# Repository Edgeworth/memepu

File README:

# Memepu

TODO fill out.

## Verymeme

### Example commands:

#### memecad

#### memelang
memelang ./src/memepile/{integral,memory,pointer,stdintf,vector,string,token,main}.meme

### Running tests
Run run.py to run the tests for both SCHEMATIC and non-SCHEMATIC verilog
configurations.

### Adding new symbols
Process for adding a new leaf module for verymeme:
1. Decide which Kicad symbol to use. If it's a new symbol, add data to
   pcb/kicadtools/ and generate using that.
2. Write a verilog module corresponding to that symbol
3. Write a mapping in memecad_map.json for the verilog module and kicad symbol.
4. Add it as a verilator module in verymeme/verilog/CMakeLists.txt
5. Add it to the SymbiYosys file in verymeme/verilog/formally_verify.sby

### Fuzzing
Build with:

export PFX=./

cmake -DUSE_AFL=yes -DCMAKE_BUILD_TYPE=Release $PFX/verymeme
AFL_SKIP_CPUFREQ=yes AFL_PRELOAD=/usr/local/lib/afl/libdislocator.so \
  afl-fuzz -m 1024M -i $PFX/verymeme/test_data/memelang/parsing -o memelang_fuzz \
  -x $PFX/verymeme/assets/afl/memelang.dict -- ./memelang @@

Or for persistent mode:
cmake -DUSE_AFL=clang -DCMAKE_BUILD_TYPE=Release $PFX/verymeme

AFL_SKIP_CPUFREQ=yes AFL_PRELOAD=/usr/local/lib/afl/libdislocator.so \
  afl-fuzz -m 1024M -i $PFX/verymeme/test_data/memelang/parsing -o memelang_fuzz \
  -x $PFX/verymeme/assets/afl/memelang.dict -t 100 -- ./memelang

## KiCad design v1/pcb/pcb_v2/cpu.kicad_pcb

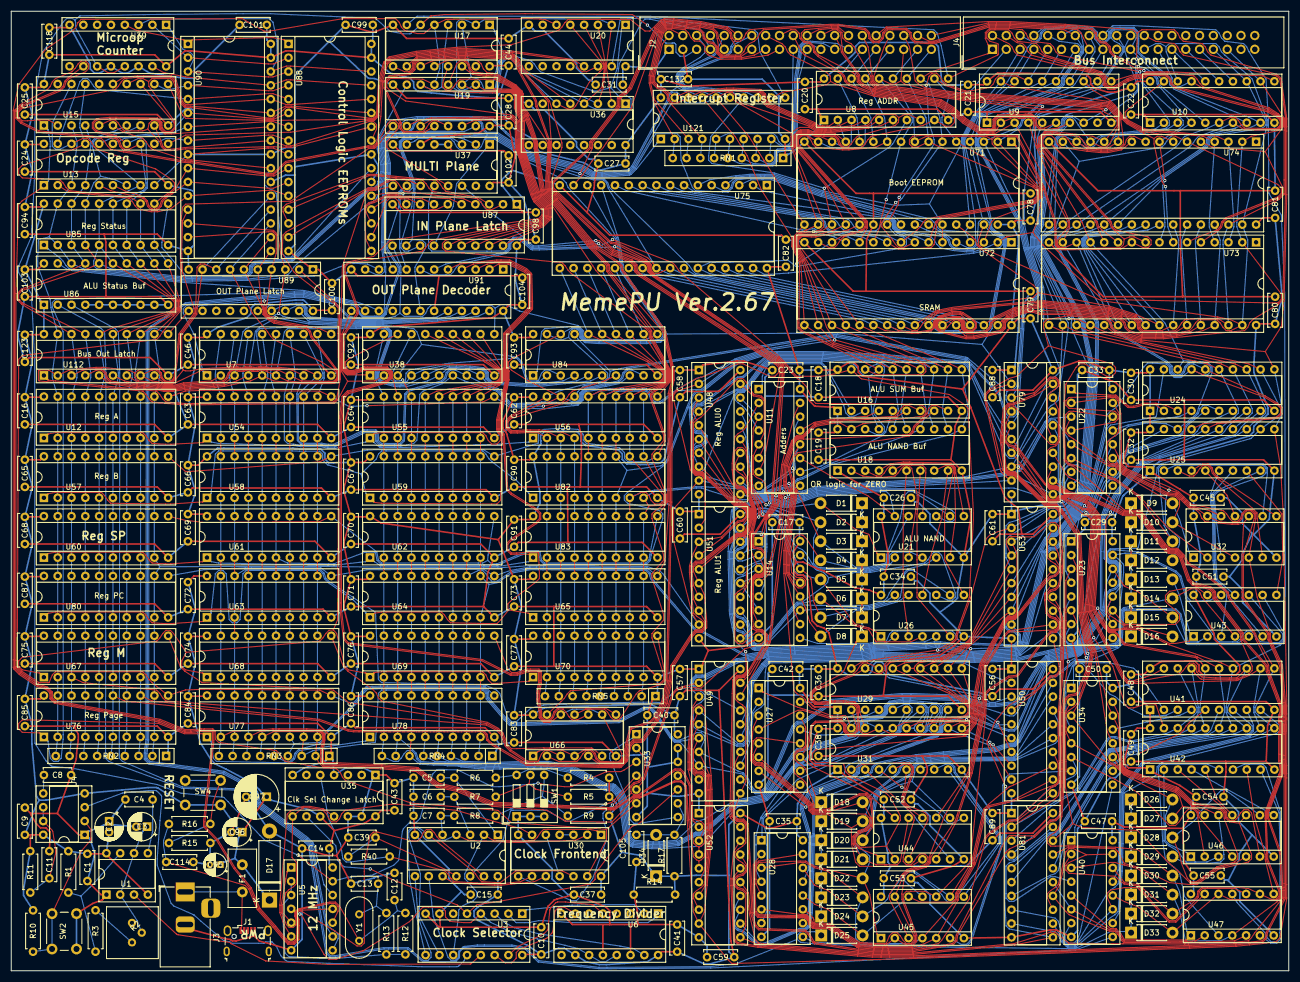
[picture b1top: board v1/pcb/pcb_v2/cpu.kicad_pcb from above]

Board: 2 copper layers, 235.0 x 176.5 mm, 268 parts (0 on the bottom side), 340 nets.

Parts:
C1, C5, C6, C7, C9, C10, C11, C14, C15, C16, C17, C18, C19, C20, C21, C22, C23, C24, C25, C26, C27, C28, C29, C30, C31, C32, C33, C34, C35, C36, C37, C38, C40, C41, C42, C43, C44, C45, C46, C47, C48, C49, C50, C51, C52, C53, C54, C55, C56, C57, C58, C59, C60, C61, C62, C63, C64, C65, C66, C67, C68, C69, C70, C71, C72, C73, C74, C75, C76, C77, C78, C79, C80, C81, C82, C83, C84, C85, C86, C87, C88, C89, C90, C91, C92, C93, C94, C98, C99, C100, C101, C102, C103, C104, C114, C118, C123, C132: 0.1uF; C_Disc_D6.0mm_W2.5mm_P5.00mm
C2, C3: 1uF; CP_Radial_D5.0mm_P2.00mm
C4, C8: 10nF; C_Disc_D5.0mm_W2.5mm_P5.00mm
C12, C13: 27pF; C_Disc_D4.7mm_W2.5mm_P5.00mm
C39: 1nF; C_Disc_D5.0mm_W2.5mm_P5.00mm
C95: 10uF; CP_Radial_D4.0mm_P2.00mm
C96: 100uF; CP_Radial_D5.0mm_P2.00mm
C97: 470uF; CP_Radial_D8.0mm_P3.80mm
C105: 10nF; C_Disc_D6.0mm_W2.5mm_P5.00mm
D1, D2, D3, D4, D5, D6, D7, D8, D9, D10, D11, D12, D13, D14, D15, D16, D18, D19, D20, D21, D22, D23, D24, D25, D26, D27, D28, D29, D30, D31, D32, D33, D34: D; D_DO-41_SOD81_P7.62mm_Horizontal
D17: 5.6V; D_5W_P12.70mm_Horizontal
F1: 0.65A; C_Disc_D10.5mm_W5.0mm_P5.00mm
J1: Conn_01x05; USB_Micro-B_Wuerth_629105150521
J2, J4: Conn_02x20_Odd_Even; IDC-Header_2x20_P2.54mm_Vertical
J3: Conn_01x03; BarrelJack_Horizontal
R1, R3, R13: 1K; R_Axial_DIN0207_L6.3mm_D2.5mm_P7.62mm_Horizontal
R2: 1M; Akizuki-Denshi Potentiometer
R4, R5, R9, R10, R14, R15: 100K; R_Axial_DIN0207_L6.3mm_D2.5mm_P7.62mm_Horizontal
R6, R7, R8, R11, R12, R16, R17, R40: 1M; R_Axial_DIN0207_L6.3mm_D2.5mm_P7.62mm_Horizontal
RN1: 10K; R_Array_SIP9
RN2, RN3, RN4, RN5: 100K; R_Array_SIP9
SW1: SW_DIP_x03 - Clock Source Select; SW_DIP_SPSTx03_Slide_9.78x9.8mm_W7.62mm_P2.54mm
SW2, SW4: SW_Push; SW_PUSH_6mm_H7.3mm
U1: LM555; DIP-8_W7.62mm_Socket
U2: 74HC14; DIP-14_W7.62mm_Socket
U3: 74151; DIP-16_W7.62mm_Socket
U4: LM555 - Button Clock; DIP-8_W7.62mm_Socket
U5: 74HC04; DIP-14_W7.62mm_Socket
U6, U39: 74HC590; DIP-16_W7.62mm_Socket
U7, U38, U84, U87, U89, U112: 74LS574; DIP-20_W7.62mm_Socket
U8, U9, U10, U12, U48, U49, U50, U51, U52, U53, U54, U55, U56, U57, U58, U59, U60, U61, U62, U63, U64, U65, U67, U68, U69, U70, U76, U77, U78, U79, U80, U81, U82, U83, U85, U121: 74HCT574; DIP-20_W7.62mm_Socket
U11, U14, U22, U23, U27, U28, U34, U40: 74LS283; DIP-16_W7.62mm_Socket
U13, U15: 74LS273; DIP-20_W7.62mm_Socket
U16, U18, U24, U25, U29, U31, U41, U42, U86: 74HC245; DIP-20_W7.62mm_Socket
U17, U19, U20, U36: 74HC238; DIP-16_W7.62mm_Socket
U21, U26, U32, U43, U44, U45, U46, U47: 74HC00; DIP-14_W7.62mm_Socket
U30: 74HC86; DIP-14_W7.62mm_Socket
U33: 74LS08; DIP-14_W7.62mm_Socket
U35: 74LS107; DIP-14_W7.62mm_Socket
U37: 74LS138; DIP-16_W7.62mm_Socket
U66: 74LS32; DIP-14_W7.62mm_Socket
U71, U88, U90: SST39SF040; DIP-32_W15.24mm_Socket
U72, U73, U74, U75: 628128; DIP-32_W15.24mm_Socket
U91: 74LS154; DIP-24_W7.62mm_Socket
Y1: 12MHz; Crystal_HC49-U_Vertical

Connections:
/ADDR0: J2.29, U8.19, U71.12
/ADDR1: J2.31, U8.18, U71.11
/ADDR2: J2.33, U8.17, U71.10, U72.12, U73.12, U74.12, U75.12
/ADDR3: J2.35, U8.16, U71.9, U72.11, U73.11, U74.11, U75.11
/ADDR4: J2.37, U8.15, U71.8, U72.10, U73.10, U74.10, U75.10
/ADDR5: J2.39, U8.14, U71.7, U72.9, U73.9, U74.9, U75.9
/ADDR6: J4.1, U8.13, U71.6, U72.8, U73.8, U74.8, U75.8
/ADDR7: J4.3, U8.12, U71.5, U72.7, U73.7, U74.7, U75.7
/ADDR8: J4.5, U9.19, U71.27, U72.6, U73.6, U74.6, U75.6
/ADDR9: J4.7, U9.18, U71.26, U72.5, U73.5, U74.5, U75.5
/ADDR10: J4.9, U9.17, U71.23, U72.27, U73.27, U74.27, U75.27
/ADDR11: J4.11, U9.16, U71.25, U72.26, U73.26, U74.26, U75.26
/ADDR12: J4.13, U9.15, U71.4, U72.23, U73.23, U74.23, U75.23
/ADDR13: J4.15, U9.14, U71.28, U72.25, U73.25, U74.25, U75.25
/ADDR14: J4.17, U9.13, U71.29, U72.4, U73.4, U74.4, U75.4
/ADDR15: J4.19, U9.12, U71.3, U72.28, U73.28, U74.28, U75.28
/ADDR16: J4.21, U10.19, U71.2, U72.3, U73.3, U74.3, U75.3
/ADDR17: J4.23, U10.18, U71.30, U72.31, U73.31, U74.31, U75.31
/ADDR18: J4.25, U10.17, U71.1, U72.2, U73.2, U74.2, U75.2
/ADDR19: J4.27, U10.16
/ADDR20: J4.29, U10.15
/ADDR21: J4.31, U10.14
/ADDR22: J4.33, U10.13, U72.22, U73.22, U74.22, U75.22
/ADDR23: J4.35, U10.12, U72.30, U73.30, U74.30, U75.30
/ADDR_IN_CLK: U8.11, U9.11, U10.11, U17.7
/ALU0_IN_CLK: U17.10, U48.11, U49.11, U50.11, U79.11
/ALU1_IN_CLK: U17.9, U51.11, U52.11, U53.11, U81.11
/ALU/A0: D1.2, U11.5, U21.1, U48.19
/ALU/A1: D2.2, U11.3, U21.4, U48.18
/ALU/A2: D3.2, U11.14, U21.9, U48.17
/ALU/A3: D4.2, U11.12, U21.12, U48.16
/ALU/A4: D5.2, U14.5, U26.1, U48.15
/ALU/A5: D6.2, U14.3, U26.4, U48.14
/ALU/A6: D7.2, U14.14, U26.9, U48.13
/ALU/A7: D8.2, U14.12, U26.12, U48.12
/ALU/A8: D9.2, U22.5, U32.1, U49.19
/ALU/A9: D10.2, U22.3, U32.4, U49.18
/ALU/A10: D11.2, U22.14, U32.9, U49.17
/ALU/A11: D12.2, U22.12, U32.12, U49.16
/ALU/A12: D13.2, U23.5, U43.1, U49.15
/ALU/A13: D14.2, U23.3, U43.4, U49.14
/ALU/A14: D15.2, U23.14, U43.9, U49.13
/ALU/A15: D16.2, U23.12, U43.12, U49.12
/ALU/A16: D18.2, U27.5, U44.1, U50.19
/ALU/A17: D19.2, U27.3, U44.4, U50.18
/ALU/A18: D20.2, U27.14, U44.9, U50.17
/ALU/A19: D21.2, U27.12, U44.12, U50.16
/ALU/A20: D22.2, U28.5, U45.1, U50.15
/ALU/A21: D23.2, U28.3, U45.4, U50.14
/ALU/A22: D24.2, U28.14, U45.9, U50.13
/ALU/A23: D25.2, U28.12, U45.12, U50.12
/ALU/A24: D26.2, U34.5, U46.1, U79.19
/ALU/A25: D27.2, U34.3, U46.4, U79.18
/ALU/A26: D28.2, U34.14, U46.9, U79.17
/ALU/A27: D29.2, U34.12, U46.12, U79.16
/ALU/A28: D30.2, U40.5, U47.1, U79.15
/ALU/A29: D31.2, U40.3, U47.4, U79.14
/ALU/A30: D32.2, U40.14, U47.9, U79.13
/ALU/A31: D33.2, U40.12, U47.12, U79.12
/ALU/B0: U11.6, U21.2, U51.19
/ALU/B1: U11.2, U21.5, U51.18
/ALU/B2: U11.15, U21.10, U51.17
/ALU/B3: U11.11, U21.13, U51.16
/ALU/B4: U14.6, U26.2, U51.15
/ALU/B5: U14.2, U26.5, U51.14
/ALU/B6: U14.15, U26.10, U51.13
/ALU/B7: U14.11, U26.13, U51.12
/ALU/B8: U22.6, U32.2, U52.19
/ALU/B9: U22.2, U32.5, U52.18
/ALU/B10: U22.15, U32.10, U52.17
/ALU/B11: U22.11, U32.13, U52.16
/ALU/B12: U23.6, U43.2, U52.15
/ALU/B13: U23.2, U43.5, U52.14
/ALU/B14: U23.15, U43.10, U52.13
/ALU/B15: U23.11, U43.13, U52.12
/ALU/B16: U27.6, U44.2, U53.19
/ALU/B17: U27.2, U44.5, U53.18
/ALU/B18: U27.15, U44.10, U53.17
/ALU/B19: U27.11, U44.13, U53.16
/ALU/B20: U28.6, U45.2, U53.15
/ALU/B21: U28.2, U45.5, U53.14
/ALU/B22: U28.15, U45.10, U53.13
/ALU/B23: U28.11, U45.13, U53.12
/ALU/B24: U34.6, U46.2, U81.19
/ALU/B25: U34.2, U46.5, U81.18
/ALU/B26: U34.15, U46.10, U81.17
/ALU/B27: U34.11, U46.13, U81.16
/ALU/B28: U40.6, U47.2, U81.15
/ALU/B29: U40.2, U47.5, U81.14
/ALU/B30: U40.15, U47.10, U81.13
/ALU/B31: U40.11, U47.13, U81.12
/ALU/CARRY0: U11.9, U14.7
/ALU/CARRY1: U14.9, U22.7
/ALU/CARRY2: U22.9, U23.7
/ALU/CARRY3: U23.9, U27.7
/ALU/CARRY4: U27.9, U28.7
/ALU/CARRY5: U28.9, U34.7
/ALU/CARRY6: U34.9, U40.7
/ALU/CARRY_OUT: U40.9, U86.2
/ALU/NAND0: U18.2, U21.3
/ALU/NAND1: U18.3, U21.6
/ALU/NAND2: U18.4, U21.8
/ALU/NAND3: U18.5, U21.11
/ALU/NAND4: U18.6, U26.3
/ALU/NAND5: U18.7, U26.6
/ALU/NAND6: U18.8, U26.8
/ALU/NAND7: U18.9, U26.11
/ALU/NAND8: U25.2, U32.3
/ALU/NAND9: U25.3, U32.6
/ALU/NAND10: U25.4, U32.8
/ALU/NAND11: U25.5, U32.11
/ALU/NAND12: U25.6, U43.3
/ALU/NAND13: U25.7, U43.6
/ALU/NAND14: U25.8, U43.8
/ALU/NAND15: U25.9, U43.11
/ALU/NAND16: U31.2, U44.3
/ALU/NAND17: U31.3, U44.6
/ALU/NAND18: U31.4, U44.8
/ALU/NAND19: U31.5, U44.11
/ALU/NAND20: U31.6, U45.3
/ALU/NAND21: U31.7, U45.6
/ALU/NAND22: U31.8, U45.8
/ALU/NAND23: U31.9, U45.11
/ALU/NAND24: U42.2, U46.3
/ALU/NAND25: U42.3, U46.6
/ALU/NAND26: U42.4, U46.8
/ALU/NAND27: U42.5, U46.11
/ALU/NAND28: U42.6, U47.3
/ALU/NAND29: U42.7, U47.6
/ALU/NAND30: U42.8, U47.8
/ALU/NAND31: U42.9, U47.11
/ALU/SUM0: U11.4, U16.2
/ALU/SUM1: U11.1, U16.3
/ALU/SUM2: U11.13, U16.4
/ALU/SUM3: U11.10, U16.5
/ALU/SUM4: U14.4, U16.6
/ALU/SUM5: U14.1, U16.7
/ALU/SUM6: U14.13, U16.8
/ALU/SUM7: U14.10, U16.9
/ALU/SUM8: U22.4, U24.2
/ALU/SUM9: U22.1, U24.3
/ALU/SUM10: U22.13, U24.4
/ALU/SUM11: U22.10, U24.5
/ALU/SUM12: U23.4, U24.6
/ALU/SUM13: U23.1, U24.7
/ALU/SUM14: U23.13, U24.8
/ALU/SUM15: U23.10, U24.9
/ALU/SUM16: U27.4, U29.2
/ALU/SUM17: U27.1, U29.3
/ALU/SUM18: U27.13, U29.4
/ALU/SUM19: U27.10, U29.5
/ALU/SUM20: U28.4, U29.6
/ALU/SUM21: U28.1, U29.7
/ALU/SUM22: U28.13, U29.8
/ALU/SUM23: U28.10, U29.9
/ALU/SUM24: U34.4, U41.2
/ALU/SUM25: U34.1, U41.3
/ALU/SUM26: U34.13, U41.4
/ALU/SUM27: U34.10, U41.5
/ALU/SUM28: U40.4, U41.6
/ALU/SUM29: U40.1, U41.7
/ALU/SUM30: U40.13, U41.8
/ALU/SUM31: U40.10, U41.9
/ALU/ZERO_OUT: U2.8, U86.3
/A_IN_CLK: U12.11, U17.14, U54.11, U55.11, U56.11
/BUS0: J2.2, RN2.9, U8.2, U12.2, U12.19, U13.3, U15.3, U16.18, U18.18, U48.2, U51.2, U57.2, U57.19, U60.2, U60.19, U67.2, U67.19, U71.13, U72.13, U76.2, U76.19, U80.2, U80.19, U85.2, U85.19, U86.18, U112.19, U121.19
/BUS1: J2.4, RN2.8, U8.3, U12.3, U12.18, U13.4, U15.4, U16.17, U18.17, U48.3, U51.3, U57.3, U57.18, U60.3, U60.18, U67.3, U67.18, U71.14, U72.14, U76.3, U76.18, U80.3, U80.18, U85.3, U85.18, U86.17, U112.18, U121.18
/BUS2: J2.6, RN2.7, U8.4, U12.4, U12.17, U13.7, U15.7, U16.16, U18.16, U48.4, U51.4, U57.4, U57.17, U60.4, U60.17, U67.4, U67.17, U71.15, U72.15, U76.4, U76.17, U80.4, U80.17, U85.4, U85.17, U86.16, U112.17, U121.17
/BUS3: J2.8, RN2.6, U8.5, U12.5, U12.16, U13.8, U15.8, U16.15, U18.15, U48.5, U51.5, U57.5, U57.16, U60.5, U60.16, U67.5, U67.16, U71.17, U72.17, U76.5, U76.16, U80.5, U80.16, U85.5, U85.16, U86.15, U112.16, U121.16
/BUS4: J2.10, RN2.5, U8.6, U12.6, U12.15, U13.13, U15.13, U16.14, U18.14, U48.6, U51.6, U57.6, U57.15, U60.6, U60.15, U67.6, U67.15, U71.18, U72.18, U76.6, U76.15, U80.6, U80.15, U85.6, U85.15, U86.14, U112.15, U121.15
/BUS5: J2.12, RN2.4, U8.7, U12.7, U12.14, U13.14, U15.14, U16.13, U18.13, U48.7, U51.7, U57.7, U57.14, U60.7, U60.14, U67.7, U67.14, U71.19, U72.19, U76.7, U76.14, U80.7, U80.14, U85.7, U85.14, U86.13, U112.14, U121.14
/BUS6: J2.14, RN2.3, U8.8, U12.8, U12.13, U13.17, U15.17, U16.12, U18.12, U48.8, U51.8, U57.8, U57.13, U60.8, U60.13, U67.8, U67.13, U71.20, U72.20, U76.8, U76.13, U80.8, U80.13, U85.8, U85.13, U86.12, U112.13, U121.13
/BUS7: J2.16, RN2.2, U8.9, U12.9, U12.12, U13.18, U15.18, U16.11, U18.11, U48.9, U51.9, U57.9, U57.12, U60.9, U60.12, U67.9, U67.12, U71.21, U72.21, U76.9, U76.12, U80.9, U80.12, U85.9, U85.12, U86.11, U112.12, U121.12
/BUS8: J2.18, RN3.9, U7.19, U9.2, U24.18, U25.18, U49.2, U52.2, U54.2, U54.19, U58.2, U58.19, U61.2, U61.19, U63.2, U63.19, U68.2, U68.19, U73.13, U77.2, U77.19
/BUS9: J2.20, RN3.8, U7.18, U9.3, U24.17, U25.17, U49.3, U52.3, U54.3, U54.18, U58.3, U58.18, U61.3, U61.18, U63.3, U63.18, U68.3, U68.18, U73.14, U77.3, U77.18
/BUS10: J2.22, RN3.7, U7.17, U9.4, U24.16, U25.16, U49.4, U52.4, U54.4, U54.17, U58.4, U58.17, U61.4, U61.17, U63.4, U63.17, U68.4, U68.17, U73.15, U77.4, U77.17
/BUS11: J2.24, RN3.6, U7.16, U9.5, U24.15, U25.15, U49.5, U52.5, U54.5, U54.16, U58.5, U58.16, U61.5, U61.16, U63.5, U63.16, U68.5, U68.16, U73.17, U77.5, U77.16
/BUS12: J2.26, RN3.5, U7.15, U9.6, U24.14, U25.14, U49.6, U52.6, U54.6, U54.15, U58.6, U58.15, U61.6, U61.15, U63.6, U63.15, U68.6, U68.15, U73.18, U77.6, U77.15
/BUS13: J2.28, RN3.4, U7.14, U9.7, U24.13, U25.13, U49.7, U52.7, U54.7, U54.14, U58.7, U58.14, U61.7, U61.14, U63.7, U63.14, U68.7, U68.14, U73.19, U77.7, U77.14
/BUS14: J2.30, RN3.3, U7.13, U9.8, U24.12, U25.12, U49.8, U52.8, U54.8, U54.13, U58.8, U58.13, U61.8, U61.13, U63.8, U63.13, U68.8, U68.13, U73.20, U77.8, U77.13
/BUS15: J2.32, RN3.2, U7.12, U9.9, U24.11, U25.11, U49.9, U52.9, U54.9, U54.12, U58.9, U58.12, U61.9, U61.12, U63.9, U63.12, U68.9, U68.12, U73.21, U77.9, U77.12
/BUS16: J2.34, RN4.9, U10.2, U29.18, U31.18, U38.19, U50.2, U53.2, U55.2, U55.19, U59.2, U59.19, U62.2, U62.19, U64.2, U64.19, U69.2, U69.19, U74.13, U78.2, U78.19
/BUS17: J2.36, RN4.8, U10.3, U29.17, U31.17, U38.18, U50.3, U53.3, U55.3, U55.18, U59.3, U59.18, U62.3, U62.18, U64.3, U64.18, U69.3, U69.18, U74.14, U78.3, U78.18
/BUS18: J2.38, RN4.7, U10.4, U29.16, U31.16, U38.17, U50.4, U53.4, U55.4, U55.17, U59.4, U59.17, U62.4, U62.17, U64.4, U64.17, U69.4, U69.17, U74.15, U78.4, U78.17
/BUS19: J2.40, RN4.6, U10.5, U29.15, U31.15, U38.16, U50.5, U53.5, U55.5, U55.16, U59.5, U59.16, U62.5, U62.16, U64.5, U64.16, U69.5, U69.16, U74.17, U78.5, U78.16
/BUS20: J4.2, RN4.5, U10.6, U29.14, U31.14, U38.15, U50.6, U53.6, U55.6, U55.15, U59.6, U59.15, U62.6, U62.15, U64.6, U64.15, U69.6, U69.15, U74.18, U78.6, U78.15
/BUS21: J4.4, RN4.4, U10.7, U29.13, U31.13, U38.14, U50.7, U53.7, U55.7, U55.14, U59.7, U59.14, U62.7, U62.14, U64.7, U64.14, U69.7, U69.14, U74.19, U78.7, U78.14
/BUS22: J4.6, RN4.3, U10.8, U29.12, U31.12, U38.13, U50.8, U53.8, U55.8, U55.13, U59.8, U59.13, U62.8, U62.13, U64.8, U64.13, U69.8, U69.13, U74.20, U78.8, U78.13
/BUS23: J4.8, RN4.2, U10.9, U29.11, U31.11, U38.12, U50.9, U53.9, U55.9, U55.12, U59.9, U59.12, U62.9, U62.12, U64.9, U64.12, U69.9, U69.12, U74.21, U78.9, U78.12
/BUS24: J4.10, RN5.9, U41.18, U42.18, U56.2, U56.19, U65.2, U65.19, U70.2, U70.19, U75.13, U79.2, U81.2, U82.2, U82.19, U83.2, U83.19, U84.19
/BUS25: J4.12, RN5.8, U41.17, U42.17, U56.3, U56.18, U65.3, U65.18, U70.3, U70.18, U75.14, U79.3, U81.3, U82.3, U82.18, U83.3, U83.18, U84.18
/BUS26: J4.14, RN5.7, U41.16, U42.16, U56.4, U56.17, U65.4, U65.17, U70.4, U70.17, U75.15, U79.4, U81.4, U82.4, U82.17, U83.4, U83.17, U84.17
/BUS27: J4.16, RN5.6, U41.15, U42.15, U56.5, U56.16, U65.5, U65.16, U70.5, U70.16, U75.17, U79.5, U81.5, U82.5, U82.16, U83.5, U83.16, U84.16
/BUS28: J4.18, RN5.5, U41.14, U42.14, U56.6, U56.15, U65.6, U65.15, U70.6, U70.15, U75.18, U79.6, U81.6, U82.6, U82.15, U83.6, U83.15, U84.15
/BUS29: J4.20, RN5.4, U41.13, U42.13, U56.7, U56.14, U65.7, U65.14, U70.7, U70.14, U75.19, U79.7, U81.7, U82.7, U82.14, U83.7, U83.14, U84.14
/BUS30: J4.22, RN5.3, U41.12, U42.12, U56.8, U56.13, U65.8, U65.13, U70.8, U70.13, U75.20, U79.8, U81.8, U82.8, U82.13, U83.8, U83.13, U84.13
/BUS31: J4.24, RN5.2, U41.11, U42.11, U56.9, U56.12, U65.9, U65.12, U70.9, U70.12, U75.21, U79.9, U81.9, U82.9, U82.12, U83.9, U83.12, U84.12
/B_IN_CLK: U17.13, U57.11, U58.11, U59.11, U82.11
/CARRY_IN: U11.7, U37.12
/CLK: J2.5, U5.13, U17.6, U33.3, U39.11, U39.13
/Clock/1.5MHZ_CLK: U3.1, U6.2
/Clock/3MHZ_CLK: U3.2, U6.1
/Clock/6MHZ_CLK: U3.3, U6.15
/Clock/12MHZ_CLK: U3.4, U5.4, U6.11, U6.13
/Clock/47_KHZ_CLK: U3.14, U6.7
/Clock/187KHZ_CLK: U3.15, U6.5
/Clock/AC_TR: C3.1, R2.2, U1.2, U1.6
/Clock/ADJ_CLK: U1.3, U3.13
/Clock/BTN_CLK: U3.12, U4.3
/Clock/PRE_CLK: U3.5, U33.10, U35.9
/Clock/SEL0: U2.2, U3.11, U30.1
/Clock/SEL1: U2.4, U3.10, U30.2
/Clock/SEL2: U2.6, U3.9, U30.12
/Control Logic/CTRL0: U87.2, U88.13
/Control Logic/CTRL1: U87.3, U88.14
/Control Logic/CTRL2: U87.4, U88.15
/Control Logic/CTRL3: U87.5, U88.17
/Control Logic/CTRL4: U87.6, U88.18
/Control Logic/CTRL5: U87.7, U88.19
/Control Logic/CTRL6: U87.8, U88.20
/Control Logic/CTRL7: U87.9, U88.21
/Control Logic/CTRL8: U7.2, U38.2, U84.2, U89.2, U90.13, U112.2
/Control Logic/CTRL9: U7.3, U38.3, U84.3, U89.3, U90.14, U112.3
/Control Logic/CTRL10: U7.4, U38.4, U84.4, U89.4, U90.15, U112.4
/Control Logic/CTRL11: U7.5, U38.5, U84.5, U89.5, U90.17, U112.5
/Control Logic/CTRL12: U7.6, U38.6, U84.6, U89.6, U90.18, U112.6
/Control Logic/CTRL13: U7.7, U38.7, U84.7, U89.7, U90.19, U112.7
/Control Logic/CTRL14: U7.8, U38.8, U84.8, U89.8, U90.20, U112.8
/Control Logic/CTRL15: U7.9, U38.9, U84.9, U89.9, U90.21, U112.9
/Control Logic/CTRL_IN0: U17.1, U19.1, U20.1, U36.1, U87.19
/Control Logic/CTRL_IN1: U17.2, U19.2, U20.2, U36.2, U87.18
/Control Logic/CTRL_IN2: U17.3, U19.3, U20.3, U36.3, U87.17
/Control Logic/CTRL_IN3: U17.4, U19.6, U20.5, U36.6, U87.16
/Control Logic/CTRL_IN4: U5.11, U17.5, U19.5, U20.6, U87.15
/Control Logic/CTRL_MULTI0: U37.1, U87.14
/Control Logic/CTRL_MULTI1: U37.2, U87.13
/Control Logic/CTRL_MULTI2: U37.3, U87.12, U91.18
/Control Logic/CTRL_OUT0: U89.19, U91.23
/Control Logic/CTRL_OUT1: U89.18, U91.22
/Control Logic/CTRL_OUT2: U89.17, U91.21
/Control Logic/CTRL_OUT3: U89.16, U91.20
/Control Logic/IN decoder/~S4: U5.10, U36.5
/Control Logic/MICROOP0: U39.15, U88.29, U90.29
/Control Logic/MICROOP1: U39.1, U88.3, U90.3
/Control Logic/MICROOP2: U39.2, U88.2, U90.2
/Control Logic/MICROOP3: U39.3, U88.30, U90.30
/Control Logic/MICROOP4: U39.4, U88.1, U90.1
/Control Logic/MMU_IN_CLK: U5.9, U19.15
/Control Logic/OP0: U13.2, U88.12, U90.12
/Control Logic/OP1: U13.5, U88.11, U90.11
/Control Logic/OP2: U13.6, U88.10, U90.10
/Control Logic/OP3: U13.9, U88.9, U90.9
/Control Logic/OP4: U13.12, U88.8, U90.8
/Control Logic/OP5: U13.15, U88.7, U90.7
/Control Logic/OP6: U13.16, U88.6, U90.6
/Control Logic/OP7: U13.19, U88.5, U90.5
/Control Logic/OP8: U15.2, U88.27, U90.27
/Control Logic/OP9: U15.5, U88.26, U90.26
/Control Logic/OP10: U15.6, U88.23, U90.23
/Control Logic/OP11: U15.9, U88.25, U90.25
/Control Logic/OP12: U15.12, U88.4, U90.4
/Control Logic/OP13: U15.15, U88.28, U90.28
/Control Logic/OPCODE0_IN_CLK: U13.11, U20.14
/Control Logic/OPCODE1_IN_CLK: U15.11, U20.13
/Control Logic/~BUS0_OUT_NCLK: U37.11, U112.1
/Control Logic/~BUS1_OUT_NCLK: U7.1, U37.10
/Control Logic/~BUS2_OUT_NCLK: U37.9, U38.1
/Control Logic/~BUS3_OUT_NCLK: U37.7, U84.1
/Control Logic/~RESET_UOP_COUNT_NCLK: U37.13, U39.10
/INT0: J2.13, RN1.9, U121.2
/INT1: J2.15, RN1.8, U121.3
/INT2: J2.17, RN1.7, U121.4
/INT3: J2.19, RN1.6, U121.5
/INT4: J2.21, RN1.5, U121.6
/INT5: J2.23, RN1.4, U121.7
/INT6: J2.25, RN1.3, U121.8
/INT7: J2.27, RN1.2, U121.9
/INT_IN_CLK: U20.15, U121.11
/M0_IN_CLK: U19.13, U66.2
/M1_IN_CLK: U19.12, U66.5
/M2_IN_CLK: U19.11, U66.10
/M3_IN_CLK: U19.10, U66.13
/M_IN_CLK: U19.14, U66.1, U66.4, U66.9, U66.12
/PAGE_IN_CLK: U19.9, U76.11, U77.11, U78.11
/PC_IN_CLK: U17.11, U63.11, U64.11, U65.11, U80.11
/Registers/Register M/REG_IN0_OR: U66.3, U67.11
/Registers/Register M/REG_IN1_OR: U66.6, U68.11
/Registers/Register M/REG_IN2_OR: U66.8, U69.11
/Registers/Register M/REG_IN3_OR: U66.11, U70.11
/SP_IN_CLK: U17.12, U60.11, U61.11, U62.11, U83.11
/STATUS_IN_CLK: U19.7, U85.11
/~ALU_STATUS_OUT_NCLK: U86.19, U91.15
/~A_OUT_NCLK: U12.1, U54.1, U55.1, U56.1, U91.2
/~B_OUT_NCLK: U57.1, U58.1, U59.1, U82.1, U91.3
/~CLK: J2.7, U5.12, U7.11, U19.4, U20.4, U36.4, U38.11, U84.11, U87.11, U89.11, U112.11
/~EEPROM_OUT_NCLK: U71.24, U91.11
/~INT_OUT_NCLK: U91.9, U121.1
/~MMU_IN_CLK: J2.9, U5.8, U72.29, U73.29, U74.29, U75.29
/~MMU_OUT_NCLK: J2.11, U72.24, U73.24, U74.24, U75.24, U91.8
/~M_OUT_NCLK: U67.1, U68.1, U69.1, U70.1, U91.13
/~NAND_OUT_NCLK: U18.19, U25.19, U31.19, U42.19, U91.7
/~PAGE_OUT_NCLK: U76.1, U77.1, U78.1, U91.14
/~PC_OUT_NCLK: U63.1, U64.1, U65.1, U80.1, U91.5
/~RESET: U13.1, U15.1, U30.13, U33.6
/~RESET_NCLK: U33.5, U37.14
/~SP_OUT_NCLK: U60.1, U61.1, U62.1, U83.1, U91.4
/~STATUS_OUT_NCLK: U85.1, U91.10
/~SUM_OUT_NCLK: U16.19, U24.19, U29.19, U41.19, U91.6
GND: C1.2, C2.1, C3.2, C4.2, C5.1, C6.1, C7.1, C8.2, C9.2, C10.2, C11.1, C12.2, C13.2, C14.2, C15.1, C16.2, C17.2, C18.2, C19.2, C20.2, C21.2, C22.2, C23.2, C24.1, C25.1, C26.2, C27.1, C28.1, C29.2, C30.2, C31.1, C32.2, C33.2, C34.2, C35.2, C36.2, C37.1, C38.2, C39.2, C40.1, C41.1, C42.2, C43.1, C44.1, C45.2, C46.1, C47.2, C48.2, C49.2, C50.2, C51.2, C52.2, C53.2, C54.2, C55.2, C56.2, C57.2, C58.2, C59.2, C60.2, C61.2, C62.2, C63.2, C64.2, C65.2, C66.2, C67.2, C68.2, C69.2, C70.2, C71.2, C72.2, C73.2, C74.2, C75.2, C76.2, C77.2, C78.1, C79.1, C80.1, C81.1, C82.1, C83.2, C84.2, C85.2, C86.2, C87.2, C88.2, C89.2, C90.2, C91.2, C92.1, C93.1, C94.2, C95.2, C96.2, C97.2, C98.1, C99.1, C100.1, C101.1, C102.1, C103.2, C104.1, C105.1, C114.1, C118.1, C123.1, C132.2, D17.2, J1.5, J2.3, J3.2, R14.1, R15.2, RN1.1, RN2.1, RN3.1, RN4.1, RN5.1, SW1.1, SW1.2, SW1.3, SW2.1, U1.1, U2.7, U3.7, U3.8, U4.1, U5.7, U6.8, U6.12, U6.14, U7.10, U8.1, U8.10, U9.1, U9.10, U10.1, U10.10, U11.8, U12.10, U13.10, U14.8, U15.10, U16.10, U17.8, U18.10, U19.8, U20.8, U21.7, U22.8, U23.8, U24.10, U25.10, U26.7, U27.8, U28.8, U29.10, U30.7, U31.10, U32.7, U33.7, U33.12, U33.13, U34.8, U35.1, U35.4, U35.7, U35.12, U35.13, U36.8, U37.4, U37.5, U37.8, U38.10, U39.8, U39.12, U39.14, U40.8, U41.10, U42.10, U43.7, U44.7, U45.7, U46.7, U47.7, U48.1, U48.10, U49.1, U49.10, U50.1, U50.10, U51.1, U51.10, U52.1, U52.10, U53.1, U53.10, U54.10, U55.10, U56.10, U57.10, U58.10, U59.10, U60.10, U61.10, U62.10, U63.10, U64.10, U65.10, U66.7, U67.10, U68.10, U69.10, U70.10, U71.16, U71.22, U72.16, U73.16, U74.16, U75.16, U76.10, U77.10, U78.10, U79.1, U79.10, U80.10, U81.1, U81.10, U82.10, U83.10, U84.10, U85.10, U86.4, U86.5, U86.6, U86.7, U86.8, U86.9, U86.10, U87.1, U87.10, U88.16, U88.22, U88.24, U89.1, U89.10, U90.16, U90.22, U90.24, U91.12, U91.19, U112.10, U121.10
unnamed: C4.1, U1.5
unnamed: C5.2, R6.1, U2.1
unnamed: C6.2, R7.1, U2.3
unnamed: C7.2, R8.1, U2.5
unnamed: C8.1, U4.5
unnamed: C11.2, R11.2, U4.6, U4.7
unnamed: C12.1, R12.2, U5.1, Y1.1
unnamed: C13.1, R13.2, Y1.2
unnamed: C39.1, R40.1, U2.11
unnamed: C105.2, D34.2, R17.2, U33.9
unnamed: C114.2, R16.1, U2.13
unnamed: D1.1, D2.1, D3.1, D4.1, D5.1, D6.1, D7.1, D8.1, D9.1, D10.1, D11.1, D12.1, D13.1, D14.1, D15.1, D16.1, D18.1, D19.1, D20.1, D21.1, D22.1, D23.1, D24.1, D25.1, D26.1, D27.1, D28.1, D29.1, D30.1, D31.1, D32.1, D33.1, U2.9
unnamed: F1.1, J1.1, J3.1
unnamed: R1.2, R3.1, U1.7
unnamed: R2.1, R3.2
unnamed: R4.2, R6.2, SW1.6
unnamed: R5.2, R7.2, SW1.5
unnamed: R8.2, R9.2, SW1.4
unnamed: R10.1, SW2.2, U4.2
unnamed: R12.1, R13.1, U5.2, U5.3
unnamed: R15.1, R16.2, SW4.1
unnamed: R40.2, U30.9, U35.5
unnamed: U2.10, U30.10
unnamed: U2.12, U33.4
unnamed: U30.3, U30.4
unnamed: U5.5, U30.6, U35.8
unnamed: U30.8, U33.2
unnamed: U30.5, U30.11
unnamed: U33.1, U33.8
unnamed: U5.6, U35.11
VCC: C1.1, C2.2, C9.1, C10.1, C14.1, C15.2, C16.1, C17.1, C18.1, C19.1, C20.1, C21.1, C22.1, C23.1, C24.2, C25.2, C26.1, C27.2, C28.2, C29.1, C30.1, C31.2, C32.1, C33.1, C34.1, C35.1, C36.1, C37.2, C38.1, C40.2, C41.2, C42.1, C43.2, C44.2, C45.1, C46.2, C47.1, C48.1, C49.1, C50.1, C51.1, C52.1, C53.1, C54.1, C55.1, C56.1, C57.1, C58.1, C59.1, C60.1, C61.1, C62.1, C63.1, C64.1, C65.1, C66.1, C67.1, C68.1, C69.1, C70.1, C71.1, C72.1, C73.1, C74.1, C75.1, C76.1, C77.1, C78.2, C79.2, C80.2, C81.2, C82.2, C83.1, C84.1, C85.1, C86.1, C87.1, C88.1, C89.1, C90.1, C91.1, C92.2, C93.2, C94.1, C95.1, C96.1, C97.1, C98.2, C99.2, C100.2, C101.2, C102.2, C103.1, C104.2, C118.2, C123.2, C132.1, D17.1, D34.1, F1.2, J2.1, R1.1, R4.1, R5.1, R9.1, R10.2, R11.1, R14.2, R17.1, SW4.2, U1.4, U1.8, U2.14, U3.16, U4.4, U4.8, U5.14, U6.10, U6.16, U7.20, U8.20, U9.20, U10.20, U11.16, U12.20, U13.20, U14.16, U15.20, U16.1, U16.20, U17.16, U18.1, U18.20, U19.16, U20.16, U21.14, U22.16, U23.16, U24.1, U24.20, U25.1, U25.20, U26.14, U27.16, U28.16, U29.1, U29.20, U30.14, U31.1, U31.20, U32.14, U33.14, U34.16, U35.10, U35.14, U36.16, U37.6, U37.16, U38.20, U39.16, U40.16, U41.1, U41.20, U42.1, U42.20, U43.14, U44.14, U45.14, U46.14, U47.14, U48.20, U49.20, U50.20, U51.20, U52.20, U53.20, U54.20, U55.20, U56.20, U57.20, U58.20, U59.20, U60.20, U61.20, U62.20, U63.20, U64.20, U65.20, U66.14, U67.20, U68.20, U69.20, U70.20, U71.31, U71.32, U72.32, U73.32, U74.32, U75.32, U76.20, U77.20, U78.20, U79.20, U80.20, U81.20, U82.20, U83.20, U84.20, U85.20, U86.1, U86.20, U87.20, U88.31, U88.32, U89.20, U90.31, U90.32, U91.24, U112.20, U121.20
